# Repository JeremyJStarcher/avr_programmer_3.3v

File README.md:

# avr_programmer_3.3v
A 3.3v programmer for AVR.  Pi Pico based

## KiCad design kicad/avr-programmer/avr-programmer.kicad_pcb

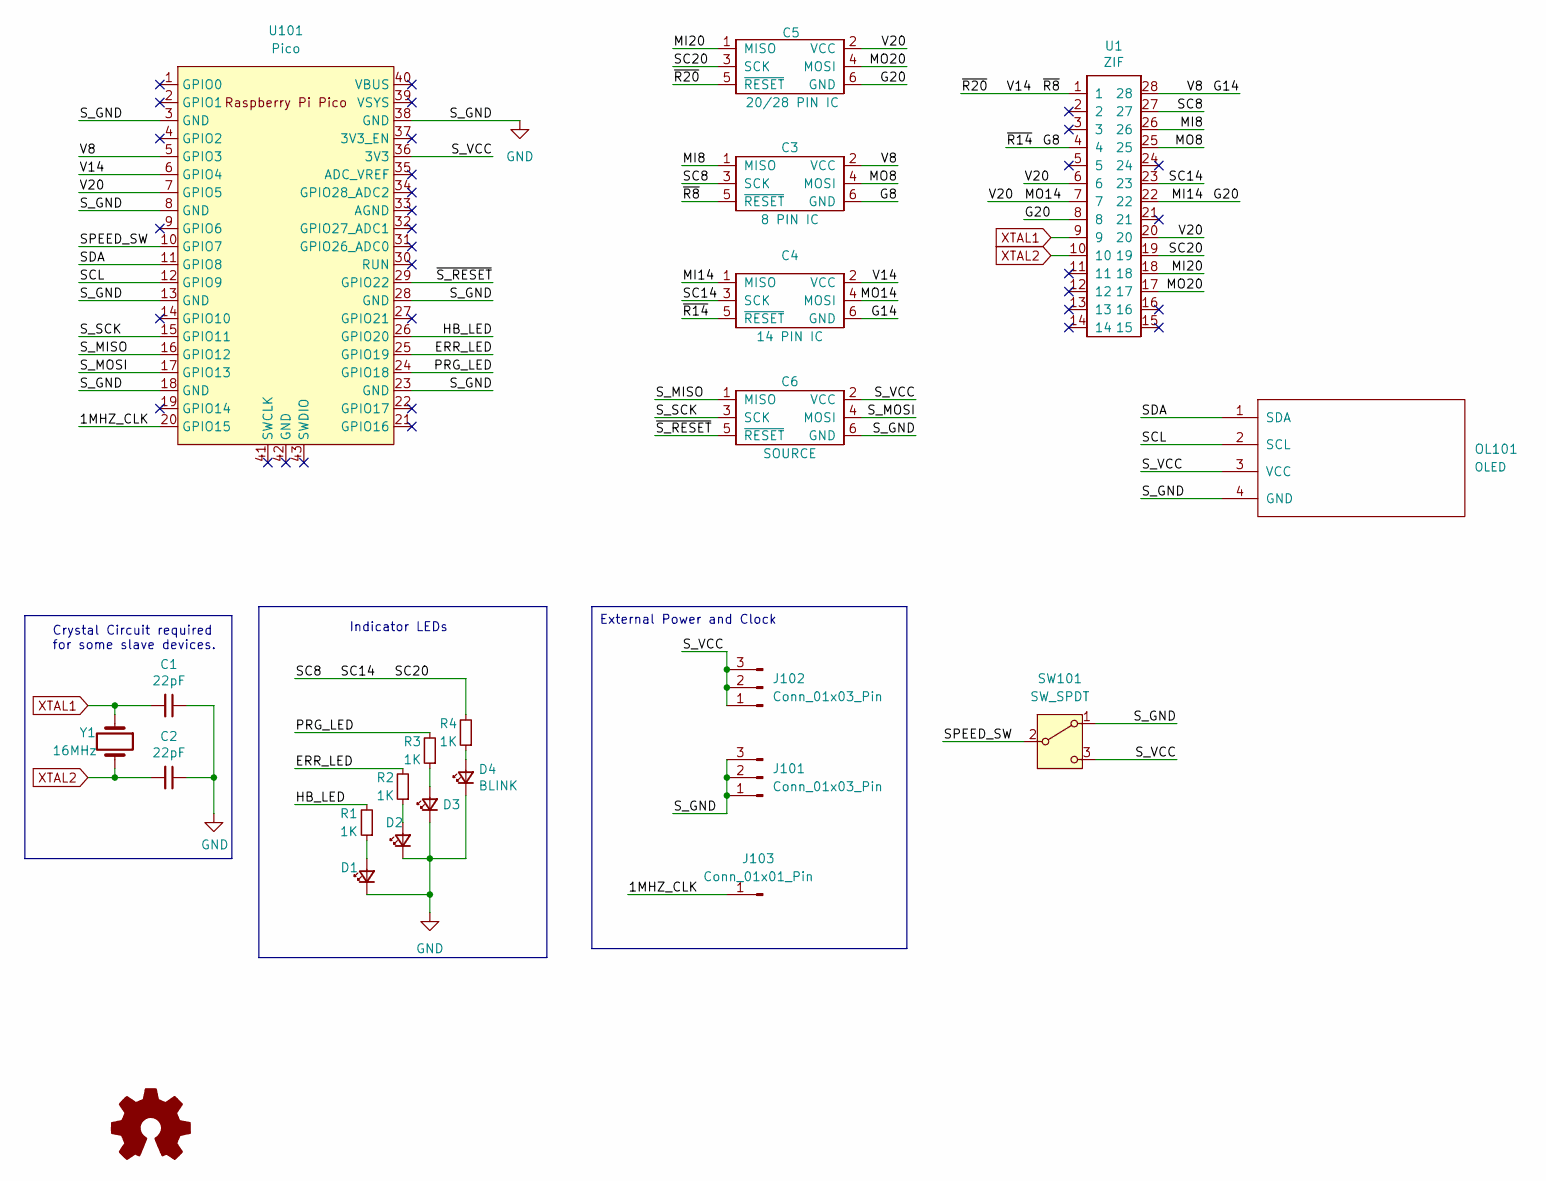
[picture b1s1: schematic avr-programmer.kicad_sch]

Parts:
C1, C2: 22pF; CP_Radial_Tantal_D5.5mm_P2.50mm
C3: 8 PIN IC; ICSP_6_pin
C4: 14 PIN IC; ICSP_6_pin
C5: 20/28 PIN IC; ICSP_6_pin
C6: SOURCE; ICSP_6_pin
D1: HB; LED_D5.0mm_Clear
D2: ERR; LED_D5.0mm_Clear
D3: PRG; LED_D5.0mm_Clear
D4: BLINK; LED_D5.0mm_Clear
J101, J102: Conn_01x03_Pin; PinHeader_1x03_P2.54mm_Vertical
J103: Conn_01x01_Pin; PinHeader_1x01_P2.54mm_Vertical
OL101: OLED; OLED_v2
R1, R2, R3, R4: 1K; R_Axial_DIN0207_L6.3mm_D2.5mm_P7.62mm_Horizontal
SW101: SW_SPDT; PinHeader_1x03_P2.54mm_Vertical
U1: ZIF; ZIF-28
U101: Pico; RPi_Pico_SMD_TH
Y1: 16MHz; Crystal_HC49-4H_Vertical

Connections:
/1MHZ_CLK: J103.1, U101.20 (GPIO15)
/ERR_LED: R2.2, U101.25 (GPIO19)
/G8: C3.6 (GND), C4.5 (~RESET), U1.4
/G14: C3.2 (VCC), C4.6 (GND), U1.28, U101.5 (GPIO3)
/G20: C4.1 (MISO), C5.6 (GND), U1.8, U1.22
/HB_LED: R1.2, U101.26 (GPIO20)
/MI8: C3.1 (MISO), U1.26
/MI20: C5.1 (MISO), U1.18
/MO8: C3.4 (MOSI), U1.25
/MO14: C4.4 (MOSI), C5.2 (VCC), U1.6, U1.7, U1.20, U101.7 (GPIO5)
/MO20: C5.4 (MOSI), U1.17
/PRG_LED: R3.2, U101.24 (GPIO18)
/SC14: C3.3 (SCK), C4.3 (SCK), C5.3 (SCK), R4.2, U1.19, U1.23, U1.27
/SCL: OL101.2 (SCL), U101.12 (GPIO9)
/SDA: OL101.1 (SDA), U101.11 (GPIO8)
/SPEED_SW: SW101.2 (B), U101.10 (GPIO7)
/S_MISO: C6.1 (MISO), U101.16 (GPIO12)
/S_MOSI: C6.4 (MOSI), U101.17 (GPIO13)
/S_SCK: C6.3 (SCK), U101.15 (GPIO11)
/S_VCC: C6.2 (VCC), J102.1, J102.2, J102.3, OL101.3 (VCC), SW101.3 (C), U101.36 (3V3)
/V14: C3.5 (~RESET), C4.2 (VCC), C5.5 (~RESET), U1.1, U101.6 (GPIO4)
/~S_RESET: C6.5 (~RESET), U101.29 (GPIO22)
GND: C1.1, C2.1, C6.6 (GND), D1.1 (K), D2.1 (K), D3.1 (K), D4.1 (K), J101.1, J101.2, J101.3, OL101.4 (GND), SW101.1 (A), U101.3 (GND), U101.8 (GND), U101.13 (GND), U101.18 (GND), U101.23 (GND), U101.28 (GND), U101.38 (GND)
unnamed: D1.2 (A), R1.1
unnamed: D2.2 (A), R2.1
unnamed: D3.2 (A), R3.1
unnamed: D4.2 (A), R4.1
XTAL1: C1.2, U1.9, Y1.1
XTAL2: C2.2, U1.10, Y1.2

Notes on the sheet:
External Power and Clock
Crystal Circuit required for some slave devices.
Indicator LEDs

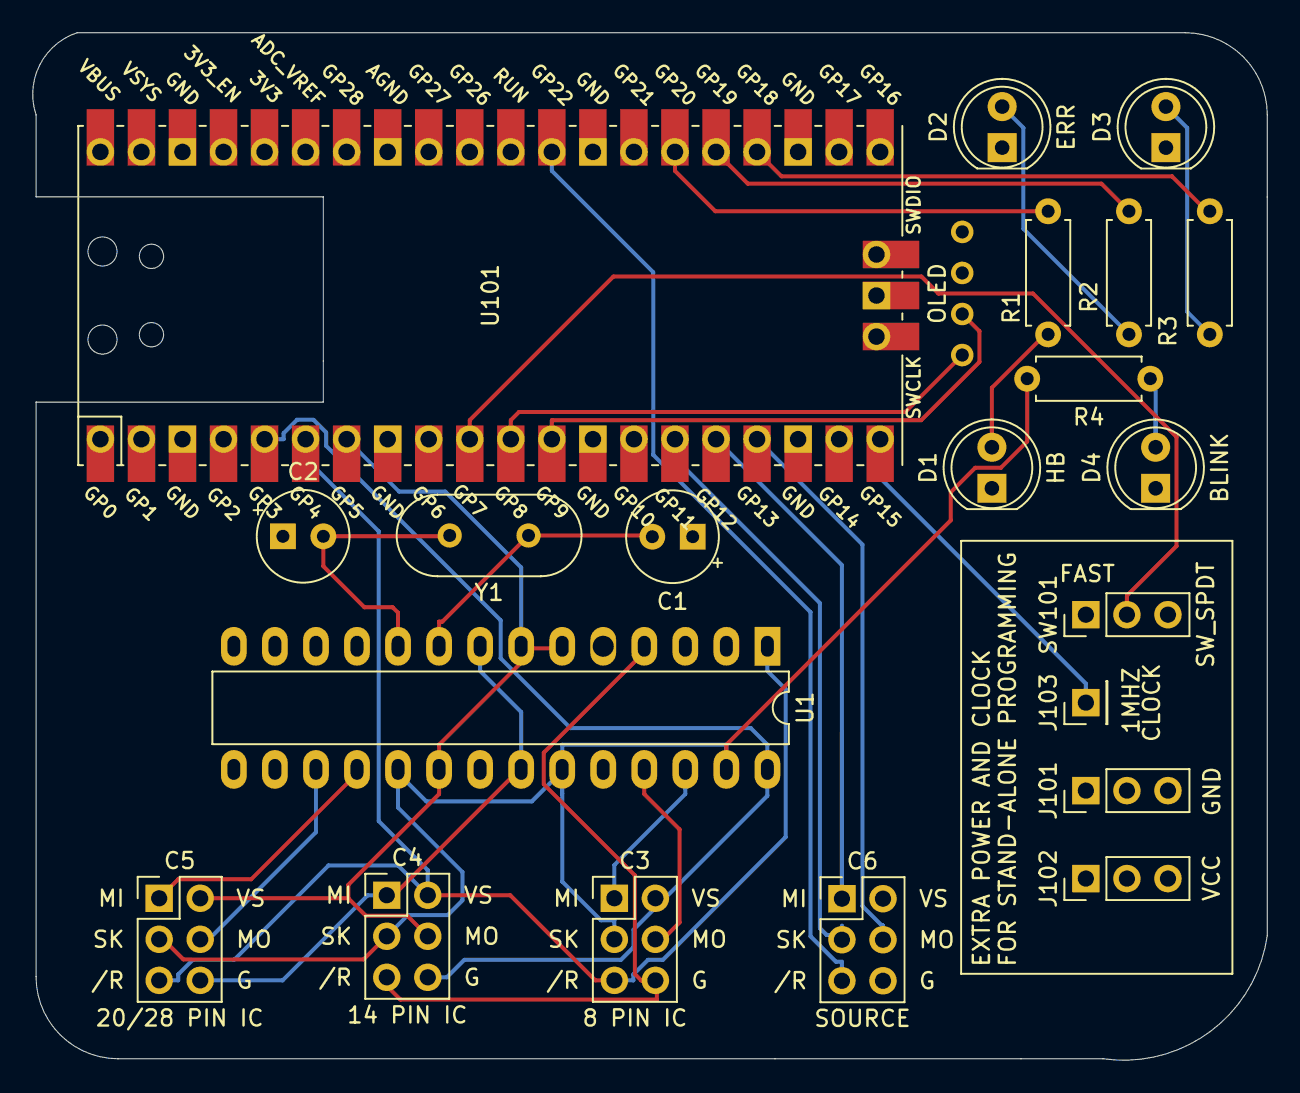
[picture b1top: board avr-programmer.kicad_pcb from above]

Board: 4 copper layers, 76.4 x 63.6 mm, 22 parts (0 on the bottom side), 29 nets.
